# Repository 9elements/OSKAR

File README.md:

# Open Source Keyboard Appliance powered by Rust

OSKAR is a firmware for the Raspberry Pi Pico that combines the 9elements picoprog project and additional HID code into a firmware for our multi-feature Macro-Keypad.

## Prerequisites

Before you can compile and use OSKAR, you need to install the following dependencies:

- Rust and Cargo: Follow the instructions on the [official Rust website](https://www.rust-lang.org/tools/install) to install Rust and Cargo.
- Install flip-link and elf2uf2

```sh
# Only Linux
sudo apt install build-essential libudev-dev pkg-config

# All systems
cargo install flip-link elf2uf2-rs
```

## Compiling the Firmware

To compile the firmware, follow these steps:

1. Clone the repository:

```sh
git clone https://github.com/9elements/OSKAR.git
cd OSKAR
```

2. Build the firmware:

```sh
cargo run --release
```

3. The compiled binary will be located in the `target/thumbv6m-none-eabi/release` directory.

## Flashing the Firmware

To flash the firmware onto the Raspberry Pi Pico, follow these steps:

1. Connect the Raspberry Pi Pico to your computer while holding the BOOTSEL button. This will put the Pico into USB mass storage mode.

2. Copy the UF2 file to the Pico:

```sh
# Linux
cp target/thumbv6m-none-eabi/release/oskar.uf2 /path/to/pi/volume

# macOS
cp target/thumbv6m-none-eabi/release/oskar.uf2 /Volumes/RPI-RP2/
```

3. The Pico will automatically reboot and start running the new firmware.

## Usage

### Layout Selection

OSKAR features a state machine that manages three different keyboard layouts. The device uses two selector switches (PIN_16 and PIN_17) to cycle between layouts. Each layout has its own LED color indicator and key configuration.

#### Pre-Configured Layouts

The firmware ships with three pre-configured layouts (fully customizable in `src/layouts.rs`):

**Layout 1 - OFF (Black LED)**

- Keyboard input disabled
- All keys inactive
- LED off (RGB: 0, 0, 0)

**Layout 2 - Navigation (Red LED)**

- Encoder: Volume control (rotate) + Mute (press)
- Key 1: Left Arrow
- Key 2: Spacebar
- Key 3: Right Arrow
- LED color: Red (RGB: 10, 0, 0)
- Ideal for presentations or video playback

**Layout 3 - Media Control (Purple LED)**

- Encoder: Volume control (rotate) + Mute (press)
- Key 1: Previous Track
- Key 2: Play/Pause
- Key 3: Next Track
- LED color: Purple (RGB: 14, 4, 13)
- Perfect for music and video control

### Customizing Layouts

Layouts are defined in `src/layouts.rs`. Each layout is a constant struct of type `KeyLayout`:

```rust
pub const LAYOUT_2: KeyLayout = KeyLayout {
    encoder_left: KeyType::Media(MediaKey::VolumeDecrement),
    encoder_right: KeyType::Media(MediaKey::VolumeIncrement),
    encoder_button: KeyType::Media(MediaKey::Mute),
    key1: KeyType::Keycode(KeyboardUsage::KeyboardLeftArrow),
    key2: KeyType::Keycode(KeyboardUsage::KeyboardSpacebar),
    key3: KeyType::Keycode(KeyboardUsage::KeyboardRightArrow),
    led_color: RGB8::new(10, 0, 0), // Red
    active: true,
};
```

To customize a layout:
1. Open `src/layouts.rs`
2. Modify any of the three `LAYOUT_X` constants
3. Change key assignments using `KeyType::Keycode()` or `KeyType::Media()`
4. Adjust LED colors with `RGB8::new(red, green, blue)` (values 0-255)
5. Rebuild and flash the firmware

**Example - Function Key Layout:**
```rust
pub const LAYOUT_2: KeyLayout = KeyLayout {
    encoder_left: KeyType::Media(MediaKey::VolumeDecrement),
    encoder_right: KeyType::Media(MediaKey::VolumeIncrement),
    encoder_button: KeyType::Media(MediaKey::Mute),
    key1: KeyType::Keycode(KeyboardUsage::KeyboardF10),
    key2: KeyType::Keycode(KeyboardUsage::KeyboardF11),
    key3: KeyType::Keycode(KeyboardUsage::KeyboardF12),
    led_color: RGB8::new(0, 10, 0), // Green
    active: true,
};
```

Available key types can be found in the `KeyboardUsage` enum (for regular keys) and `MediaKey` enum (for media controls) from the `usbd_hid` crate.

### Serial (picocom or combined mode)

Once the firmware is running, you can use any terminal program to communicate with the UART and SPI peripherals via USB. The device will appear as a USB CDC (Communications Device Class) device. Currently `/dev/ttyACM0` (macOS: `/dev/tty.usbmodemOSFC20241`) is a debug console that prints information about the Pico's current operation.

### UART Communication (picocom or combined mode)

To communicate with the UART peripheral, open the corresponding serial port (e.g., `/dev/ttyACM1` on Linux, `/dev/tty.usbmodemOSFC20243` on macOS) with your terminal program. For now the Baud is fixed at 115200 but can be changed in code. Dynamic reconfiguration is still planned.

### Using Flashrom or Flashprog (picocom or combined mode)

To interact with the Raspberry Pi Pico for reading and writing SPI flash chips, you can use tools like `flashrom` or `flashprog`. These tools support the `serprog` protocol, which allows communication over a serial interface.

1. Install `flashrom` or `flashprog` e.g.:

```sh
# Debian or Debian-based Linux distributions
sudo apt-get install flashrom

# macOS with Homebrew
brew install flashrom
```

2. Use the following command to read from the SPI flash chip:

```sh
flashrom -p serprog:dev=/dev/ttyACM2 -r backup.bin
```

This command reads the contents of the SPI flash chip and saves it to `backup.bin`.

3. Use the following command to write to the SPI flash chip:

```sh
flashrom -p serprog:dev=/dev/ttyACM2 -w firmware.bin
```

This command writes the contents of `firmware.bin` to the SPI flash chip.

Make sure to replace `/dev/ttyACM2` with the correct serial port if your device is connected to a different port or if you're on a different operating system (on macOS it will be `/dev/tty.usbmodemOSFC20245`).

## License

This project is licensed under the Apache 2.0 License. See the [LICENSE](LICENSE) file for details.

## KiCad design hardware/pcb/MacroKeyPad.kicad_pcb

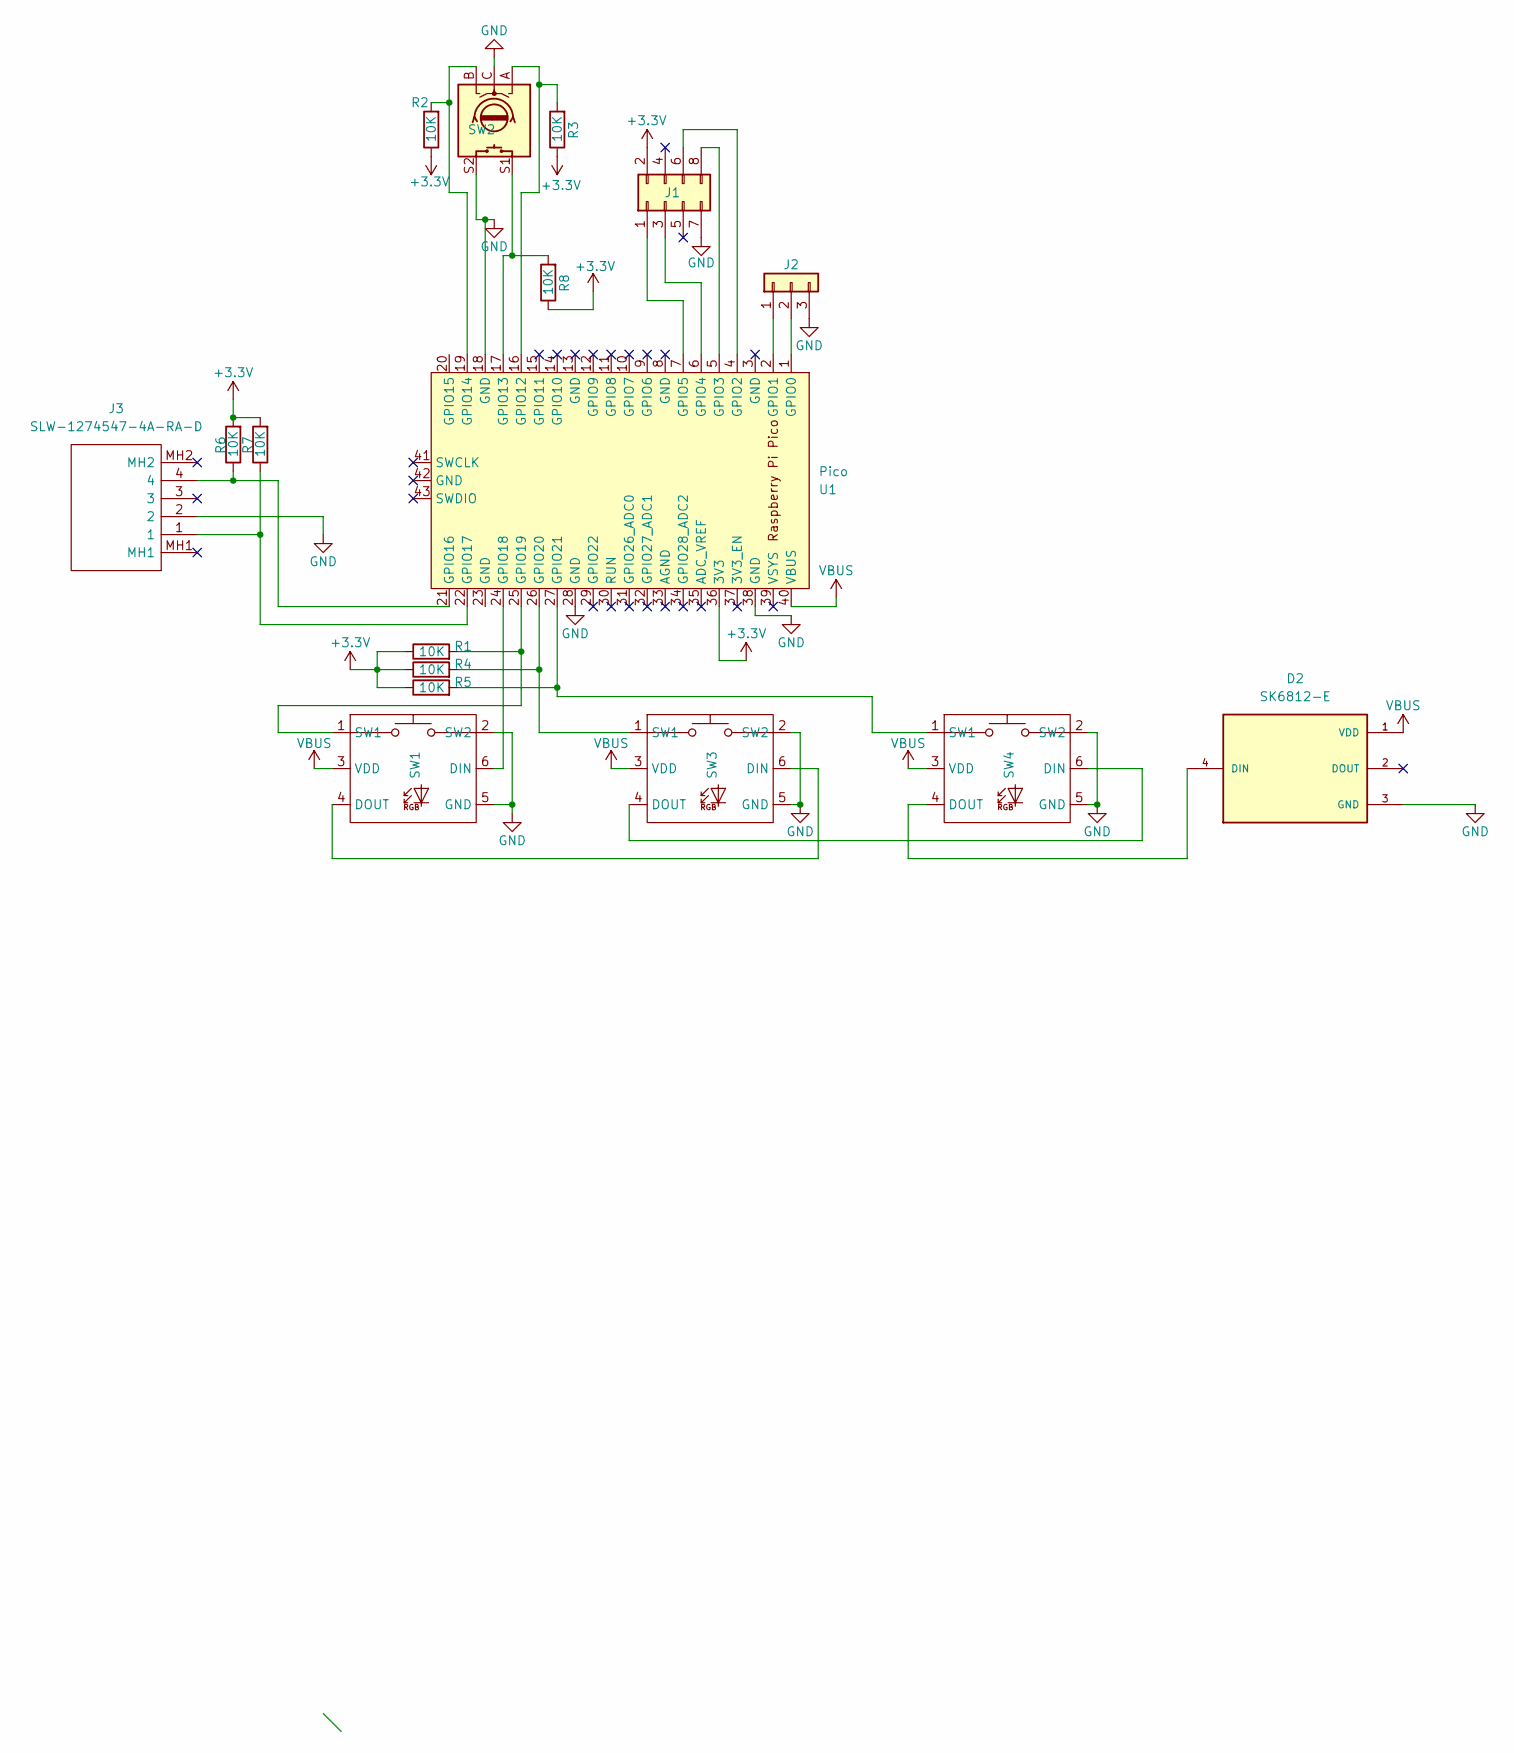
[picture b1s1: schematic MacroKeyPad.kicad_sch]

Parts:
D2: SK6812-E; LED_SK6812-E; PARTREV 2
J1: Conn_02x04_Odd_Even; IDC-Header_2x04_P2.54mm_Horizontal
J2: Conn_01x03; PinHeader_1x03_P2.54mm_Horizontal
J3: SLW-1274547-4A-RA-D; SLW12745474ARAD; Mouser Part Number 179-SLW12745474ARAD
R1, R2, R3, R4, R5, R6, R7, R8: 10K; R_0805_2012Metric_Pad1.20x1.40mm_HandSolder
SW1, SW3, SW4: Cherry_MX_SK6812_MINI_E
SW2: RotaryEncoder_Switch; RotaryEncoder_Alps_EC11E-Switch_Vertical_H20mm
U1: Pico; RPi_Pico_SMD_HEADER

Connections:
+3.3V: J1.2, R1.1, R2.1, R3.1, R4.1, R5.1, R6.2, R7.2, R8.1, U1.36 (3V3)
GND: D2.3 (GND), J1.7, J2.3, J3.2, SW1.2 (SW2), SW1.5 (GND), SW2.C, SW2.S2, SW3.2 (SW2), SW3.5 (GND), SW4.2 (SW2), SW4.5 (GND), U1.18 (GND), U1.28 (GND), U1.38 (GND)
unnamed: D2.4 (DIN), SW4.4 (DOUT)
unnamed: J1.1, U1.7 (GPIO5)
unnamed: J1.3, U1.6 (GPIO4)
unnamed: J1.6, U1.4 (GPIO2)
unnamed: J1.8, U1.5 (GPIO3)
unnamed: J2.1, U1.2 (GPIO1)
unnamed: J2.2, U1.1 (GPIO0)
unnamed: SW1.6 (DIN), U1.24 (GPIO18)
unnamed: SW1.4 (DOUT), SW3.6 (DIN)
unnamed: R1.2, SW1.1 (SW1), U1.25 (GPIO19)
unnamed: SW3.4 (DOUT), SW4.6 (DIN)
unnamed: R4.2, SW3.1 (SW1), U1.26 (GPIO20)
unnamed: R5.2, SW4.1 (SW1), U1.27 (GPIO21)
unnamed: R3.2, SW2.A, U1.16 (GPIO12)
unnamed: R8.2, SW2.S1, U1.17 (GPIO13)
unnamed: R2.2, SW2.B, U1.19 (GPIO14)
unnamed: J3.4, R6.1, U1.21 (GPIO16)
unnamed: J3.1, R7.1, U1.22 (GPIO17)
VBUS: D2.1 (VDD), SW1.3 (VDD), SW3.3 (VDD), SW4.3 (VDD), U1.40 (VBUS)

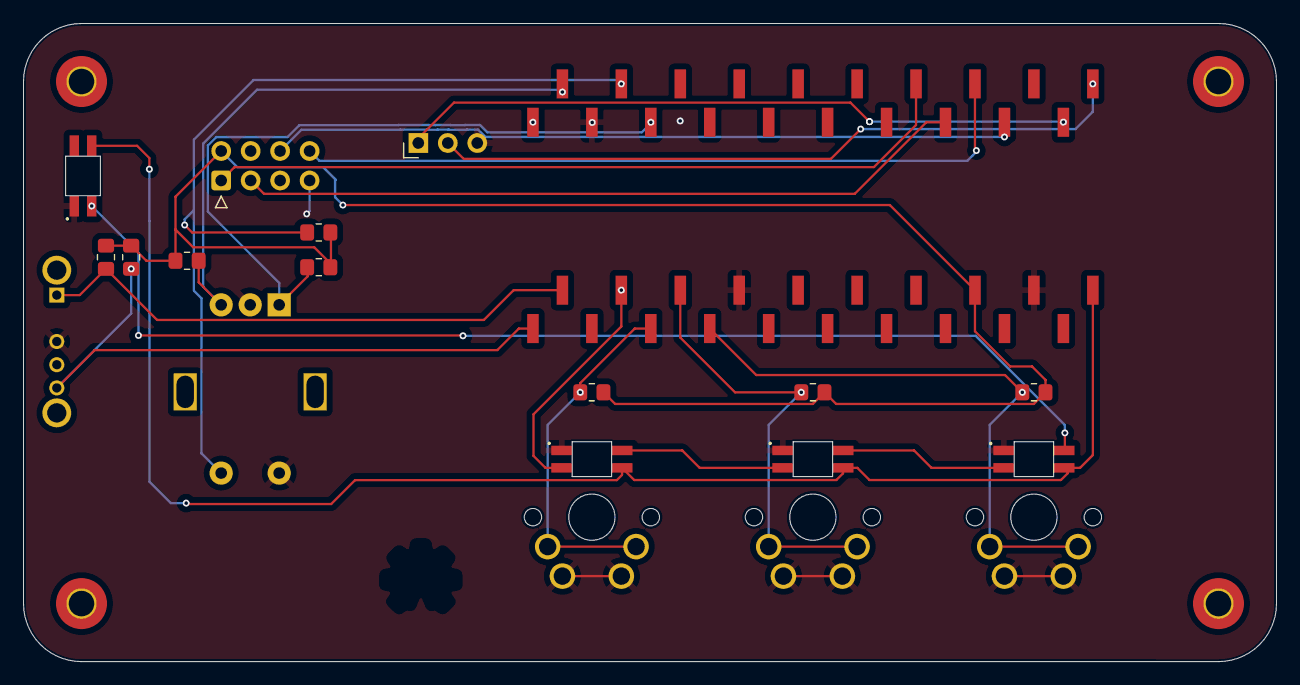
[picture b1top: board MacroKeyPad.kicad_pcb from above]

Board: 2 copper layers, 108.0 x 55.0 mm, 17 parts (0 on the bottom side), 21 nets.

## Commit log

2025-08-13 initial code push
2025-08-13 cleanup
2025-08-13 implement interrupt based task
2025-08-14 rewrite HID module
2025-08-27 deactivate optimizer for release binary
2025-08-27 add KEYLAYOUT for easier configuration
2025-08-27 update documentation
2025-09-10 add pcb project
2025-09-10 add case
2025-10-08 rework for windows compatabillity
2025-10-08 docs: update types, examples and paths
2025-10-08 refactoring
2025-10-20 Update README.md
    Minor grammatical cleanup
2025-10-22 setup multimedia keys
2025-11-11 selection switch selects keyboard layout now
2025-11-27 refactor: implement state machine for switching keyboard layouts
    Consolidate scattered state management into a centralized state machine
    that controls both LED behavior and keyboard layouts.
    Key improvements:
    - Add state.rs module with centralized DEVICE_STATE watch channel
    - Integrate LED colors with keyboard layout configurations
    - Implement 6-key rollover with key tracking
